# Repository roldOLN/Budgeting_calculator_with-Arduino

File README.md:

# Budgeting_calculator_with-Arduino
This project is designed to divide your budget to N number of days and then track how you spend that budget each day.

It is a compact, light-weight, and portable--keychain-like device that can track your budget on the go--hassle-free.

How it works:
    on the upper part of the display, you can see the "budget" text, next to it is your calculated balance for that day. Anything below that is where your regular computations will appear.

    To setup your budget per day, simply input your total budget, then press the upper left button to enter into the N days menu. Select the number of days you'll be spending your money. Once you selected your N days, the calculated budget per day will appear on the screen, after that you can go back to the main menu by clicking the upper left button again. To track your budget you can just type your spending and then press the button next to the upper left to subtract it on your budget. And there you have it! you can now track your budget on the go and hassle free!

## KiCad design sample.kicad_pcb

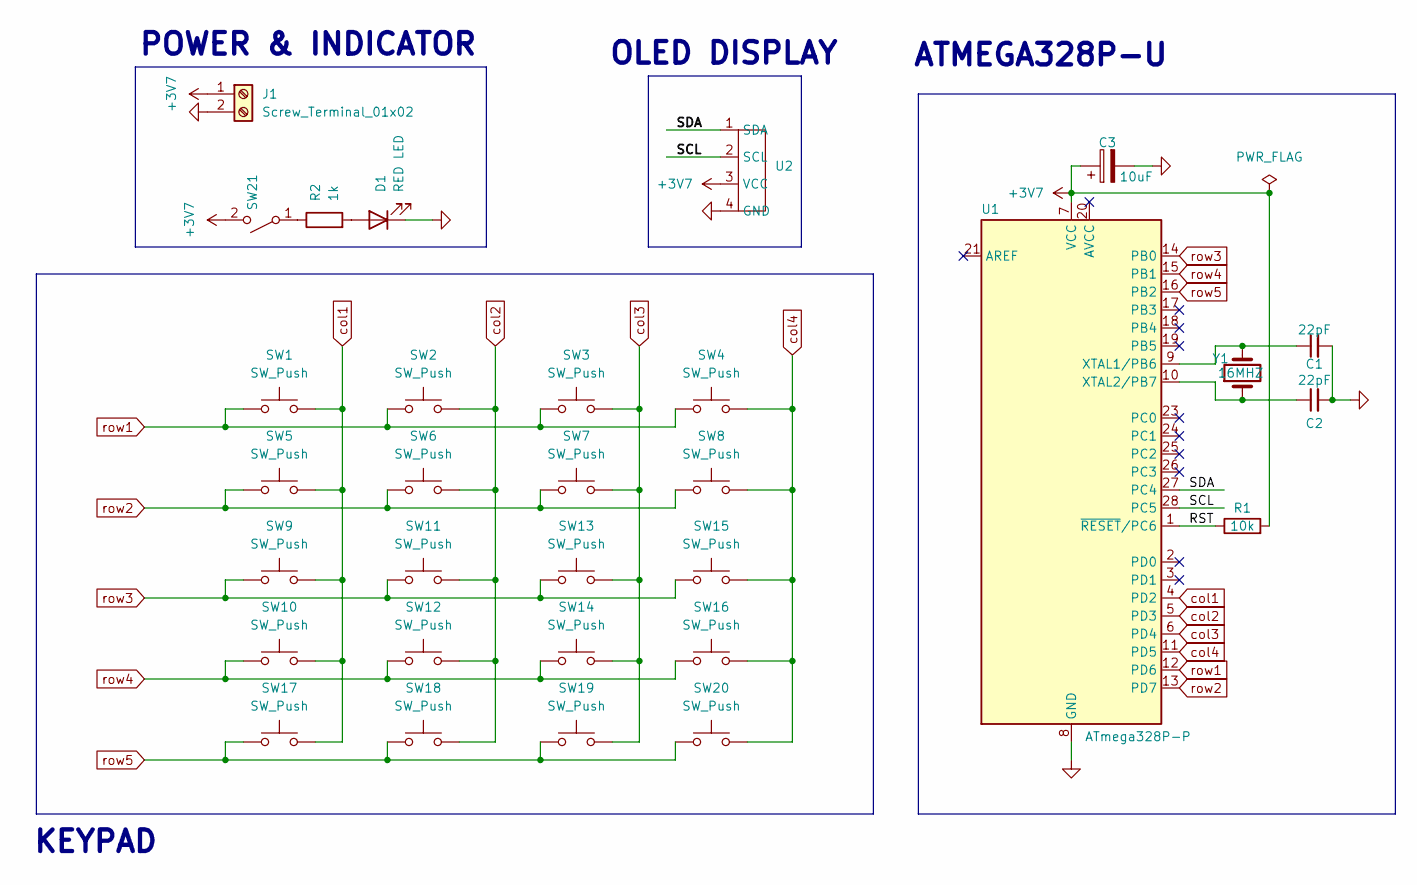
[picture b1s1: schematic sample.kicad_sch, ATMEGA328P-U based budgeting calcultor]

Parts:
C1, C2: 22pF; C_Disc_D3.0mm_W1.6mm_P2.50mm
C3: 10uF; CP_Radial_D12.5mm_P5.00mm
D1: RED LED; LED_D5.0mm_Horizontal_O1.27mm_Z3.0mm
J1: Screw_Terminal_01x02; TerminalBlock_RND_205-00276_1x02_P5.00mm_Vertical
R1: 10k; R_Axial_DIN0309_L9.0mm_D3.2mm_P2.54mm_Vertical
R2: 1k; R_Axial_DIN0309_L9.0mm_D3.2mm_P2.54mm_Vertical
SW1, SW2, SW3, SW4, SW5, SW6, SW7, SW8, SW9, SW10, SW11, SW12, SW13, SW14, SW15, SW16, SW17, SW18, SW19, SW20: SW_Push; SW_PUSH_6mm_H5mm
SW21: SW_SPST; SW_DIP_SPSTx01_Slide_9.78x4.72mm_W7.62mm_P2.54mm
U1: ATmega328P-P; DIP-28_W7.62mm
U2: SSD1306-0.91-OLED-4pin-128x32
Y1: 16MHZ; Crystal_HC49-4H_Vertical

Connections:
+3V7: C3.1, J1.1, R1.2, SW21.2 (B), U1.7 (VCC), U2.3 (VCC)
/RST: R1.1, U1.1 (~RESET/PC6)
/SCL: U1.28 (PC5), U2.2 (SCL)
/SDA: U1.27 (PC4), U2.1 (SDA)
GND: C1.2, C2.2, C3.2, D1.1 (K), J1.2, U1.8 (GND), U1.22 (GND), U2.4 (GND)
unnamed: D1.2 (A), R2.2
unnamed: R2.1, SW21.1 (A)
unnamed: C1.1, U1.9 (XTAL1/PB6), Y1.2
unnamed: C2.1, U1.10 (XTAL2/PB7), Y1.1
col1: SW1.2, SW5.2, SW9.2, SW10.2, SW17.2, U1.4 (PD2)
col2: SW2.2, SW6.2, SW11.2, SW12.2, SW18.2, U1.5 (PD3)
col3: SW3.2, SW7.2, SW13.2, SW14.2, SW19.2, U1.6 (PD4)
col4: SW4.2, SW8.2, SW15.2, SW16.2, SW20.2, U1.11 (PD5)
row1: SW1.1, SW2.1, SW3.1, SW4.1, U1.12 (PD6)
row2: SW5.1, SW6.1, SW7.1, SW8.1, U1.13 (PD7)
row3: SW9.1, SW11.1, SW13.1, SW15.1, U1.14 (PB0)
row4: SW10.1, SW12.1, SW14.1, SW16.1, U1.15 (PB1)
row5: SW17.1, SW18.1, SW19.1, SW20.1, U1.16 (PB2)

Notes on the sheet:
POWER & INDICATOR
KEYPAD
ATMEGA328P-U
OLED DISPLAY

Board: 2 copper layers, 31 parts (0 on the bottom side), 18 nets, no tracks yet.

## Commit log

2024-03-29 uploaded files
    pcb layout is still unfinished
